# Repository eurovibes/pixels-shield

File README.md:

<!-- SPDX-FileCopyrightText: 2026 Benedikt Spranger <b.spranger@linutronix.de> -->
<!-- SPDX-License-Identifier: CERN-OHL-S-2.0 -->

# pixels-shield - We need a shield for pixels!

A Arduino UNO R3 shield to control [pixels](https://github.com/eurovibes/pixels).

## License rules

pixels-shield is provided under the terms of the CERN-OHL-S license version 2
as provided in the LICENSES/CERN-OHL-S-2.0 file.

Instead of adding license boilerplates to the individual files, pixels-shield
uses SPDX license identifiers, which are machine parseable and considered
legaly equivalent.

The SPDX license identifier in pixels-shield shall be added at the first
possible line in a file which can contain a comment. This is normally the
first line except for scripts. Scripts require the #!PATH_TO_INTERPRETER tag
in the first line; place the SPDX identifier into the second line.

The SPDX license identifier is added in form of a comment.

## Copyright and License

Copyright Benedikt Spranger 2026.
This source describes Open Hardware and is licensed under the CERNOHL-S v2.
You may redistribute and modify this source and make products using it
under the terms of the CERN-OHL-S v2
(https://ohwr.org/cern ohl s v2.txt ).
This source is distributed WITHOUT ANY EXPRESS OR IMPLIED
WARRANTY, INCLUDING OF MERCHANTABILITY, SATISFACTORY
QUALITY AND FITNESS FOR A PARTICULAR PURPOSE. Please see
the CERN-OHL-S v2 for applicable conditions.
Source location: https://github.com/eurovibes/pixels-shield
As per CERN-OHL-S v2 section 4, should You produce hardware based
on this source, You must where practicable maintain the Source Location
visible on the external case of the pixels-shield or other products you make
using this source.

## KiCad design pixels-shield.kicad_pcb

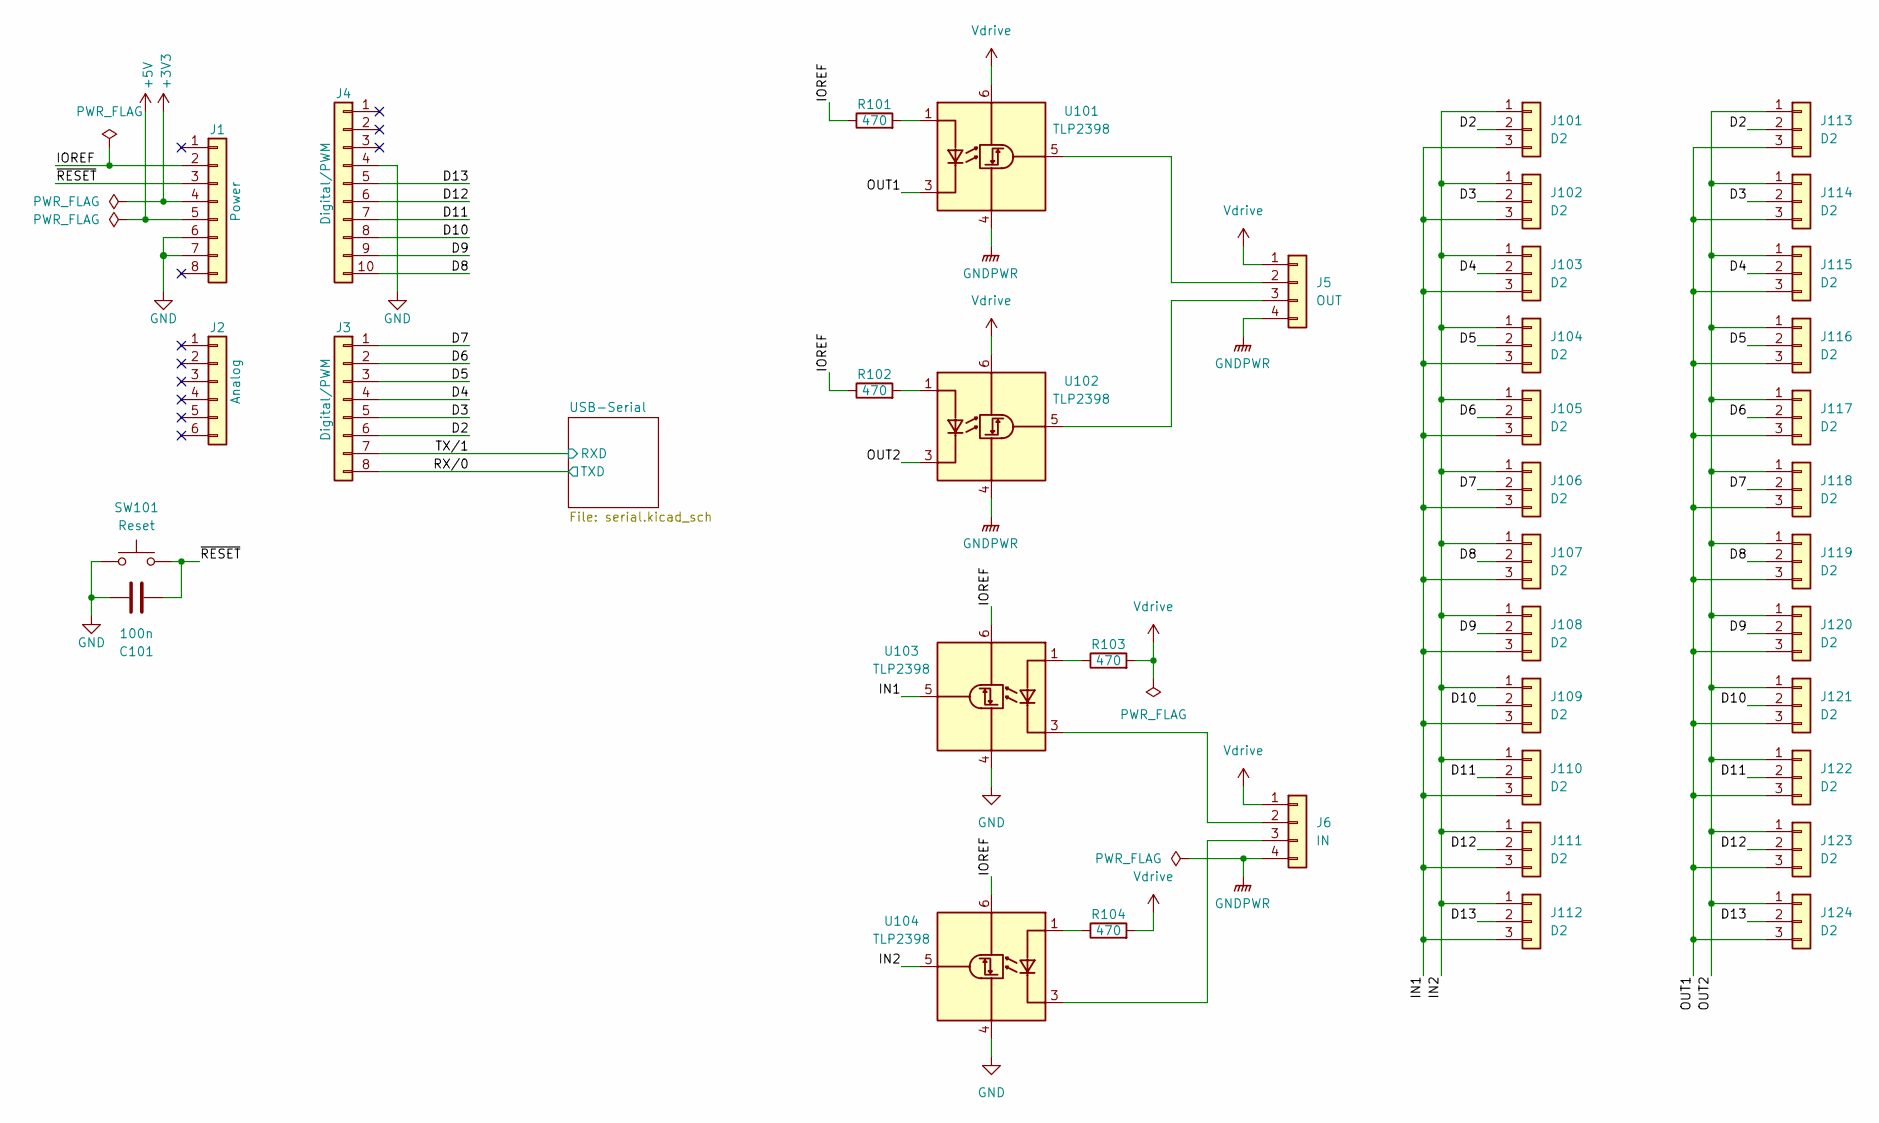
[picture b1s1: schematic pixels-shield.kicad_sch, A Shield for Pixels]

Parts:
C101: 100n; C_0402_1005Metric; mpn CL05B104KB54PNC; LCSC# C307331
J1: Power; PinSocket_1x08_P2.54mm_Vertical
J2: Analog; PinSocket_1x06_P2.54mm_Vertical
J3: Digital/PWM; PinSocket_1x08_P2.54mm_Vertical
J4: Digital/PWM; PinSocket_1x10_P2.54mm_Vertical
J5: OUT; TerminalBlock_WAGO_236-404_1x04_P5.00mm_45Degree
J6: IN; TerminalBlock_WAGO_236-404_1x04_P5.00mm_45Degree
J101, J102, J103, J104, J105, J106, J107, J108, J109, J110, J111, J112, J113, J114, J115, J116, J117, J118, J119, J120, J121, J122, J123, J124: D2; PinHeader_1x03_P1.27mm_Vertical
R101, R102, R103, R104: 470; R_0402_1005Metric; mpn 0402WGF4700TCE; LCSC# C25117
SW101: Reset; SW_Push_1P1T_XKB_TS-1187A; mpn TS-1187A-B-A-B; LCSC# C318884
U101, U102, U103, U104: TLP2398; SO-5-6_4.55x3.7mm_P1.27mm; mpn TLP2398; LCSC# C5370545

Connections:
+3V3: J1.4
+5V: J1.5
/D2: J3.6, J101.2, J113.2
/D3: J3.5, J102.2, J114.2
/D4: J3.4, J103.2, J115.2
/D5: J3.3, J104.2, J116.2
/D6: J3.2, J105.2, J117.2
/D7: J3.1, J106.2, J118.2
/D8: J4.10, J107.2, J119.2
/D9: J4.9, J108.2, J120.2
/D10: J4.8, J109.2, J121.2
/D11: J4.7, J110.2, J122.2
/D12: J4.6, J111.2, J123.2
/D13: J4.5, J112.2, J124.2
/IN1: J101.3, J102.3, J103.3, J104.3, J105.3, J106.3, J107.3, J108.3, J109.3, J110.3, J111.3, J112.3, U103.5 (VO)
/IN2: J101.1, J102.1, J103.1, J104.1, J105.1, J106.1, J107.1, J108.1, J109.1, J110.1, J111.1, J112.1, U104.5 (VO)
/IOREF: J1.2, R101.1, R102.1, U103.6 (VDD), U104.6 (VDD)
/OUT1: J113.3, J114.3, J115.3, J116.3, J117.3, J118.3, J119.3, J120.3, J121.3, J122.3, J123.3, J124.3, U101.3 (K)
/OUT2: J113.1, J114.1, J115.1, J116.1, J117.1, J118.1, J119.1, J120.1, J121.1, J122.1, J123.1, J124.1, U102.3 (K)
/RX/0: J3.8; also elsewhere on the board
/TX/1: J3.7; also elsewhere on the board
/~RESET: C101.1, J1.3, SW101.1
GND: C101.2, J1.6, J1.7, J4.4, SW101.2, U103.4 (GND), U104.4 (GND); also elsewhere on the board
GNDPWR: J5.4, J6.4, U101.4 (GND), U102.4 (GND)
unnamed: J5.2, U101.5 (VO)
unnamed: J5.3, U102.5 (VO)
unnamed: J6.2, U103.3 (K)
unnamed: J6.3, U104.3 (K)
unnamed: R101.2, U101.1 (A)
unnamed: R102.2, U102.1 (A)
unnamed: R103.1, U103.1 (A)
unnamed: R104.1, U104.1 (A)
Vdrive: J5.1, J6.1, R103.2, R104.2, U101.6 (VDD), U102.6 (VDD)

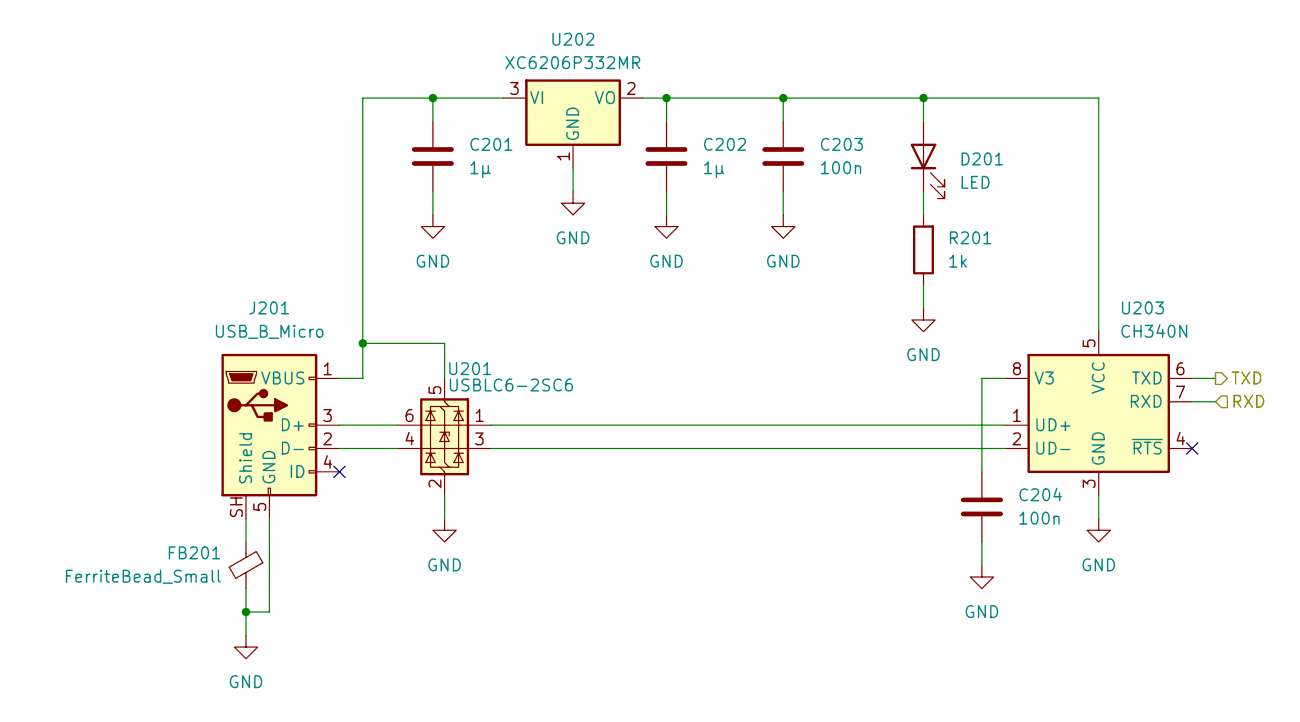
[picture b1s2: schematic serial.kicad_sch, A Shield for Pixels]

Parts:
C201, C202: 1µ; C_0603_1608Metric; mpn CL10A105KB8NNNC; LCSC# C15849
C203, C204: 100n; C_0402_1005Metric; mpn CL05B104KB54PNC; LCSC# C307331
D201: LED; LED_0603_1608Metric; mpn KT-0603R; LCSC# C2286
FB201: FerriteBead_Small; L_0603_1608Metric; mpn GZ1608D601TF; LCSC# C1002
J201: USB_B_Micro; USB_Micro-B_Amphenol_10118193-0001LF_Horizontal; mpn 10118193-0001LF; LCSC# C132562
R201: 1k; R_0402_1005Metric; mpn 0402WGF1001TCE; LCSC# C11702
U201: USBLC6-2SC6; SOT-23-6; mpn USBLC6-2SC6; LCSC# C2827654
U202: XC6206P332MR; SOT-23-3; mpn XC6206P332MR-G; LCSC# C5446
U203: CH340N; JEITA_SOIC-8_3.9x4.9mm_P1.27mm; mpn CH340N; LCSC# C2977777

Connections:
/RX/0: U203.6 (TXD); also elsewhere on the board
/TX/1: U203.7 (RXD); also elsewhere on the board
GND: C201.2, C202.2, C203.2, C204.2, FB201.2, J201.5 (GND), R201.1, U201.2 (GND), U202.1 (GND), U203.3 (GND); also elsewhere on the board
unnamed: C202.1, C203.1, D201.2 (A), U202.2 (VO), U203.5 (VCC)
unnamed: D201.1 (K), R201.2
unnamed: J201.3 (D+), U201.6 (I/O1)
unnamed: J201.2 (D-), U201.4 (I/O2)
unnamed: FB201.1, J201.SH (Shield)
unnamed: C201.1, J201.1 (VBUS), U201.5 (VBUS), U202.3 (VI)
unnamed: U201.1 (I/O1), U203.1 (UD+)
unnamed: U201.3 (I/O2), U203.2 (UD-)
unnamed: C204.1, U203.8 (V3)

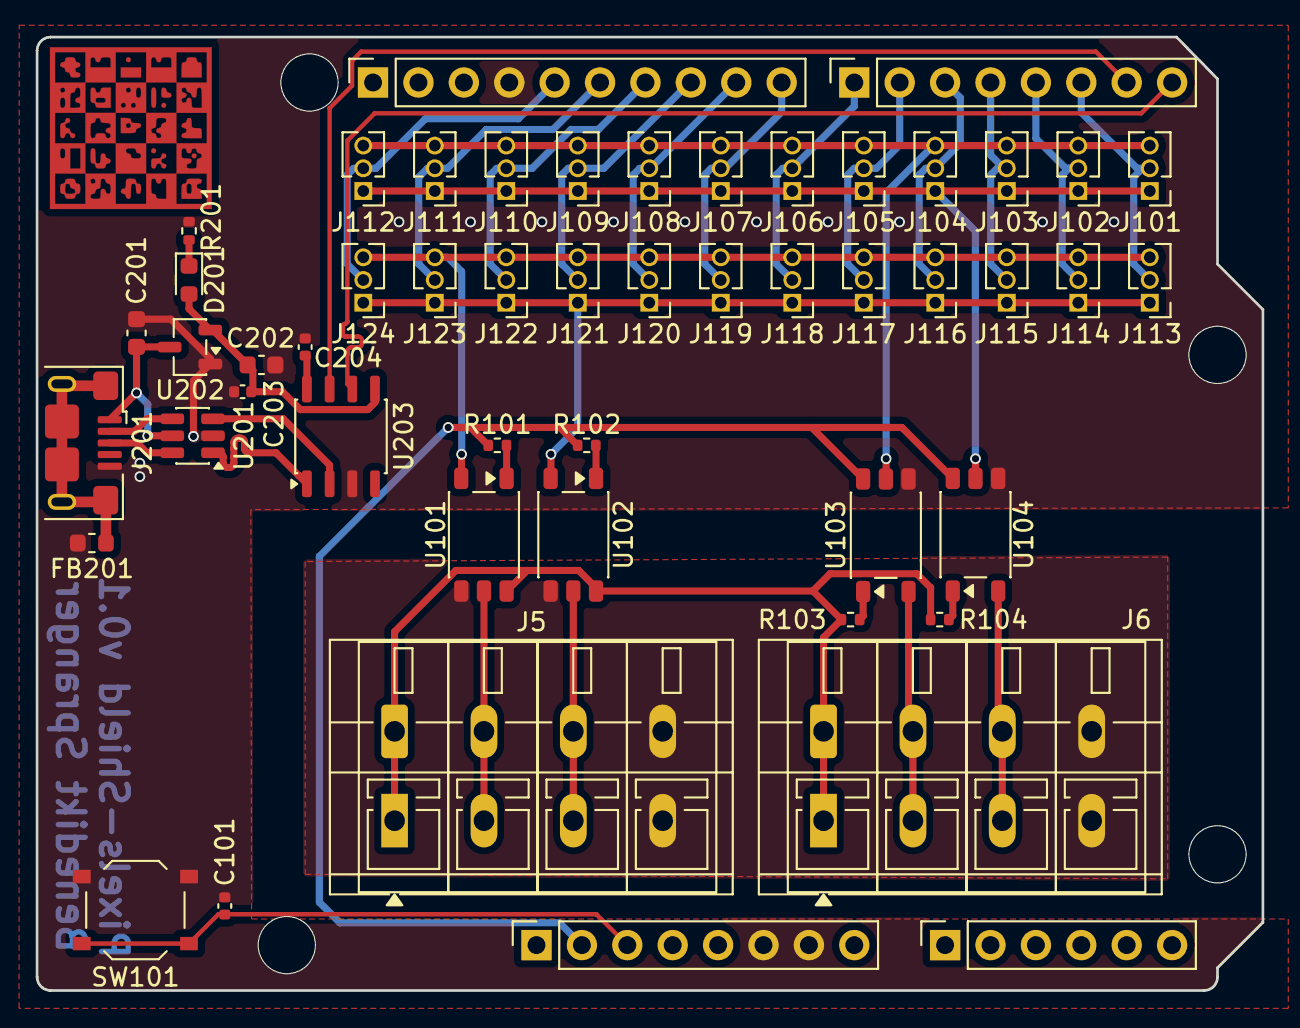
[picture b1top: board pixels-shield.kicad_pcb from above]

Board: 2 copper layers, 68.6 x 53.3 mm, 55 parts (0 on the bottom side), 40 nets.

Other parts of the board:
MH1, MH2, MH3, MH4: MountingHole_3.2mm

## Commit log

2026-04-29 Add logo
2026-04-29 Add Github actions
2026-04-29 Initial

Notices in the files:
pixels-shield.kicad_sch:
This work is licensed under the CERN-OHL-S v2
